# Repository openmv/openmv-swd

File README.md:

# openmv-swd
Serial Wire Debugger Programmer

The Serial Wire Debugger (SWD) Programmer can load firmware on up to five STM32F427/STM32F765/STM32H743 microcontrollers at the same time. The SWD Programmer is powered by the Propeller Chip. All eight cores of the Propeller Chip are used by the SWD Programmer firmware. Each SWD programming thread is run in a separate core. A master core controls the five SWD programming cores. Finally, one core provides SD card services while another core handles button debouncing and LED PWM.

If you're interested in practical code demonstrating how to load the firmware on an ST32F427/STM32F765/STM32H743 microcontroller, or generally, any ST Cortex-M4/Cortex-M7 device checkout the [SWD Code](http://github.com/openmv/openmv-swd/blob/master/module/V2/src/SWD.spin).

# openmv-swd application

* Install 7-Zip and add it to PATH.
* Install Python 2.7 and add it to PATH.
* Install Qt (to the default location).
* Install The Qt Installer Framework (to the default location).

In `/`, build the application (using the standard bare terminal):

     make.py

You'll find the installer in `module/build`.

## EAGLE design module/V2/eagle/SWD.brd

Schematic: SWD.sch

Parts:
3.3V_1,1, 3.3V_1,2, 3.3V_1,3, 3.3V_1,4, 3.3V_2,1, 3.3V_2,2, 3.3V_2,3, 3.3V_2,4, 3.3V_3,1, 3.3V_3,2, 3.3V_3,3, 3.3V_3,4, 3.3V_4,1, 3.3V_4,2, 3.3V_4,3, 3.3V_4,4, 3.3V_5,1, 3.3V_5,2, 3.3V_5,3, 3.3V_5,4: POGO_PIN_0908-4-15-20-75-14-11-0; 0908-4-15-20-75-14-11-0
C1, C2, C3, C4, C5, C6, C7, C10, C12, C13, C15, C16, C17, C18, C19, C20, C21, C22, C23, C24, C25, C27, C28, C29, C30, C31, C32, C33, C34, C35, C61, C62: 0.1uF; C0603
C8, C9: 47pF; C0603
C11, C14: 1uF; C0603
C26: 0.1uF\; C0603
C36, C37, C38, C39: 100uF; CP6.3MM
D1, D2, D3: MF-LED-0805-RED; LED0805
D4: SMBJ5.0CA; SMBJ
FRAME1: MF_FRAMEDEFAULT; MF_FRAME_DEFAULT
GND_1,1, GND_1,2, GND_1,3, GND_1,4, GND_2,1, GND_2,2, GND_2,3, GND_2,4, GND_3,1, GND_3,2, GND_3,3, GND_3,4, GND_4,1, GND_4,2, GND_4,3, GND_4,4, GND_5,1, GND_5,2, GND_5,3, GND_5,4: POGO_PIN_0908-4-15-20-75-14-11-0; 0908-4-15-20-75-14-11-0
J1: USB_TYPE-C_105450-0101; 105450-0101
J2: KLDX-0202-A; DC_PWR_JACK
L1, L2: MI0603K300R-10; L0603
R1, R2, R3, R4, R5, R6, R7, R8, R9, R14, R30, R31, R32, R33: 10K; R0603
R10: 5.1K; R0603
R11, R12: 27; R0603
R13: 4.7K; R0603
R15, R16, R17, R18, R19, R20, R21, R22, R23, R24, R25, R26, R27, R28, R29: 100; R0603
R34, R35, R36: 360; R0603
SD1: MF-MICROSD
SW1, SW2: MF-SW-TACT-6MM; TACT6MM
SWD_CLK_1,1, SWD_CLK_1,2, SWD_CLK_1,3, SWD_CLK_1,4, SWD_CLK_2,1, SWD_CLK_2,2, SWD_CLK_2,3, SWD_CLK_2,4, SWD_CLK_3,1, SWD_CLK_3,2, SWD_CLK_3,3, SWD_CLK_3,4, SWD_CLK_4,1, SWD_CLK_4,2, SWD_CLK_4,3, SWD_CLK_4,4, SWD_CLK_5,1, SWD_CLK_5,2, SWD_CLK_5,3, SWD_CLK_5,4: POGO_PIN_0908-4-15-20-75-14-11-0; 0908-4-15-20-75-14-11-0
SWD_DAT_1,1, SWD_DAT_1,2, SWD_DAT_1,3, SWD_DAT_1,4, SWD_DAT_2,1, SWD_DAT_2,2, SWD_DAT_2,3, SWD_DAT_2,4, SWD_DAT_3,1, SWD_DAT_3,2, SWD_DAT_3,3, SWD_DAT_3,4, SWD_DAT_4,1, SWD_DAT_4,2, SWD_DAT_4,3, SWD_DAT_4,4, SWD_DAT_5,1, SWD_DAT_5,2, SWD_DAT_5,3, SWD_DAT_5,4: POGO_PIN_0908-4-15-20-75-14-11-0; 0908-4-15-20-75-14-11-0
SWD_RST_1,1, SWD_RST_1,2, SWD_RST_1,3, SWD_RST_1,4, SWD_RST_2,1, SWD_RST_2,2, SWD_RST_2,3, SWD_RST_2,4, SWD_RST_3,1, SWD_RST_3,2, SWD_RST_3,3, SWD_RST_3,4, SWD_RST_4,1, SWD_RST_4,2, SWD_RST_4,3, SWD_RST_4,4, SWD_RST_5,1, SWD_RST_5,2, SWD_RST_5,3, SWD_RST_5,4: POGO_PIN_0908-4-15-20-75-14-11-0; 0908-4-15-20-75-14-11-0
U1: P8X32A-Q44; LQFP44
U2: CAT24C512WI-GT3; SOIC-8_W
U3: FT230XQ-R; FT230X_QFN-16
U4, U5, U6, U7, U8, U9, U10, U11, U12, U13, U14, U15, U16, U17, U18, U19, U20, U21, U22, U23: SN74LV4066APWR; SN74LV4066A_TSSOP-14
U24, U25, U26, U27: SSM6J507NU,LF; SSM6J507NU
U$59: MF_LOGOLOGO_TEXT; MF_LOGO_TEXT
UNIT1, UNIT2, UNIT3, UNIT4, UNIT5, UNIT6, UNIT7, UNIT8, UNIT9, UNIT10, UNIT11, UNIT12, UNIT13, UNIT14, UNIT15, UNIT16, UNIT17, UNIT18, UNIT19, UNIT20: OPENMV3
X1: ABMM-6.000MHZ-B2-T; 7MMX5MM

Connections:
3.3V: C1.P$1, C2.P$1, C3.P$1, C4.P$1, C5.P$1, C6.P$1, C7.P$1, C13.P$1, C14.P$1, C16.P$2, C17.P$2, C18.P$2, C19.P$2, C20.P$2, C21.P$2, C22.P$2, C23.P$2, C24.P$2, C25.P$2, C26.P$2, C27.P$2, C28.P$2, C29.P$2, C30.P$2, C31.P$2, C32.P$2, C33.P$2, C34.P$2, C35.P$2, C36.P$1, C37.P$1, C38.P$1, C39.P$1, C61.P$1, C62.P$1, D1.ANODE, D2.ANODE, D3.ANODE, D4.CATH (CATHODE), J2.PIN, R1.P$1, R2.P$1, R3.P$1, R4.P$1, R5.P$1, R6.P$1, R7.P$1, R8.P$1, R9.P$1, R30.P$1, R31.P$1, R32.P$1, R33.P$1, SD1.PIN4 (3.3V), U1.8 (VDD), U1.18 (VDD), U1.30 (VDD), U1.40 (VDD), U2.8 (VCC), U3.1 (VCCIO), U3.9 (RESET#), U3.10 (VCC), U4.P$14 (VCC), U5.P$14 (VCC), U6.P$14 (VCC), U7.P$14 (VCC), U8.P$14 (VCC), U9.P$14 (VCC), U10.P$14 (VCC), U11.P$14 (VCC), U12.P$14 (VCC), U13.P$14 (VCC), U14.P$14 (VCC), U15.P$14 (VCC), U16.P$14 (VCC), U17.P$14 (VCC), U18.P$14 (VCC), U19.P$14 (VCC), U20.P$14 (VCC), U21.P$14 (VCC), U22.P$14 (VCC), U23.P$14 (VCC), U24.P$1 (DRAIN), U24.P$2 (DRAIN), U24.P$5 (DRAIN), U24.P$6 (DRAIN), U24.P$8 (DRAIN), U25.P$1 (DRAIN), U25.P$2 (DRAIN), U25.P$5 (DRAIN), U25.P$6 (DRAIN), U25.P$8 (DRAIN), U26.P$1 (DRAIN), U26.P$2 (DRAIN), U26.P$5 (DRAIN), U26.P$6 (DRAIN), U26.P$8 (DRAIN), U27.P$1 (DRAIN), U27.P$2 (DRAIN), U27.P$5 (DRAIN), U27.P$6 (DRAIN), U27.P$8 (DRAIN)
3.3V_R1: 3.3V_1,1.P$1, 3.3V_2,1.P$1, 3.3V_3,1.P$1, 3.3V_4,1.P$1, 3.3V_5,1.P$1, U24.P$4 (SOURCE), U24.P$7 (SOURCE)
3.3V_R2: 3.3V_1,2.P$1, 3.3V_2,2.P$1, 3.3V_3,2.P$1, 3.3V_4,2.P$1, 3.3V_5,2.P$1, U25.P$4 (SOURCE), U25.P$7 (SOURCE)
3.3V_R3: 3.3V_1,3.P$1, 3.3V_2,3.P$1, 3.3V_3,3.P$1, 3.3V_4,3.P$1, 3.3V_5,3.P$1, U26.P$4 (SOURCE), U26.P$7 (SOURCE)
3.3V_R4: 3.3V_1,4.P$1, 3.3V_2,4.P$1, 3.3V_3,4.P$1, 3.3V_4,4.P$1, 3.3V_5,4.P$1, U27.P$4 (SOURCE), U27.P$7 (SOURCE)
3V3OUT: C12.P$1, U3.8 (3V3OUT)
!RTS: C15.P$1, U3.16 (RTS#)
CC1: J1.A5 (CC1), R10.P$1
CTRL_ROW_1: U1.44 (P3), U4.P$5 (CNTRL), U4.P$6 (CNTRL), U4.P$13 (CNTRL), U8.P$5 (CNTRL), U8.P$6 (CNTRL), U8.P$13 (CNTRL), U12.P$5 (CNTRL), U12.P$6 (CNTRL), U12.P$13 (CNTRL), U16.P$5 (CNTRL), U16.P$6 (CNTRL), U16.P$13 (CNTRL), U20.P$5 (CNTRL), U20.P$6 (CNTRL), U20.P$13 (CNTRL)
CTRL_ROW_2: U1.43 (P2), U5.P$5 (CNTRL), U5.P$6 (CNTRL), U5.P$13 (CNTRL), U9.P$5 (CNTRL), U9.P$6 (CNTRL), U9.P$13 (CNTRL), U13.P$5 (CNTRL), U13.P$6 (CNTRL), U13.P$13 (CNTRL), U17.P$5 (CNTRL), U17.P$6 (CNTRL), U17.P$13 (CNTRL), U21.P$5 (CNTRL), U21.P$6 (CNTRL), U21.P$13 (CNTRL)
CTRL_ROW_3: U1.42 (P1), U6.P$5 (CNTRL), U6.P$6 (CNTRL), U6.P$13 (CNTRL), U10.P$5 (CNTRL), U10.P$6 (CNTRL), U10.P$13 (CNTRL), U14.P$5 (CNTRL), U14.P$6 (CNTRL), U14.P$13 (CNTRL), U18.P$5 (CNTRL), U18.P$6 (CNTRL), U18.P$13 (CNTRL), U22.P$5 (CNTRL), U22.P$6 (CNTRL), U22.P$13 (CNTRL)
CTRL_ROW_4: U1.41 (P0), U7.P$5 (CNTRL), U7.P$6 (CNTRL), U7.P$13 (CNTRL), U11.P$5 (CNTRL), U11.P$6 (CNTRL), U11.P$13 (CNTRL), U15.P$5 (CNTRL), U15.P$6 (CNTRL), U15.P$13 (CNTRL), U19.P$5 (CNTRL), U19.P$6 (CNTRL), U19.P$13 (CNTRL), U23.P$5 (CNTRL), U23.P$6 (CNTRL), U23.P$13 (CNTRL)
D+: C8.P$1, J1.A6 (D+), J1.B6 (D+), R11.P$1
D-: C9.P$1, J1.A7 (D-), J1.B7 (D-), R12.P$1
GND: C1.P$2, C2.P$2, C3.P$2, C4.P$2, C5.P$2, C6.P$2, C7.P$2, C8.P$2, C9.P$2, C10.P$2, C11.P$2, C12.P$2, C13.P$2, C14.P$2, C16.P$1, C17.P$1, C18.P$1, C19.P$1, C20.P$1, C21.P$1, C22.P$1, C23.P$1, C24.P$1, C25.P$1, C26.P$1, C27.P$1, C28.P$1, C29.P$1, C30.P$1, C31.P$1, C32.P$1, C33.P$1, C34.P$1, C35.P$1, C36.P$2, C37.P$2, C38.P$2, C39.P$2, C61.P$2, C62.P$2, D4.ANODE, GND_1,1.P$1, GND_1,2.P$1, GND_1,3.P$1, GND_1,4.P$1, GND_2,1.P$1, GND_2,2.P$1, GND_2,3.P$1, GND_2,4.P$1, GND_3,1.P$1, GND_3,2.P$1, GND_3,3.P$1, GND_3,4.P$1, GND_4,1.P$1, GND_4,2.P$1, GND_4,3.P$1, GND_4,4.P$1, GND_5,1.P$1, GND_5,2.P$1, GND_5,3.P$1, GND_5,4.P$1, J1.A1 (GND), J1.A12 (GND), J1.B1 (GND), J1.B12 (GND), J2.SLEEVE1 (SLEEVE), J2.SLEEVE2 (SLEEVE_SHUNT), L2.P$2, R10.P$2, R14.P$1, R35.P$2, SD1.G0 (GND), SD1.G1 (GND), SD1.PIN6 (GND), SW1.P$3, U1.5 (VSS), U1.6 (BOE'), U1.17 (VSS), U1.27 (VSS), U1.39 (VSS), U2.1 (A0), U2.2 (A1), U2.3 (A2), U2.4 (GND), U2.7 (WP), U3.3 (GND), U3.13 (GND), U3.PAD (GND), U4.P$7 (GND), U5.P$7 (GND), U6.P$7 (GND), U7.P$7 (GND), U8.P$7 (GND), U9.P$7 (GND), U10.P$7 (GND), U11.P$7 (GND), U12.P$7 (GND), U13.P$7 (GND), U14.P$7 (GND), U15.P$7 (GND), U16.P$7 (GND), U17.P$7 (GND), U18.P$7 (GND), U19.P$7 (GND), U20.P$7 (GND), U21.P$7 (GND), U22.P$7 (GND), U23.P$7 (GND), X1.P$2 (GND), X1.P$4 (GND)
I2C_SCL: R9.P$2, U1.35 (P28), U2.6 (SCL)
I2C_SDA: R8.P$2, U1.36 (P29), U2.5 (SDA)
IRQ: R2.P$2, SD1.PIN8 (IRQ)
LED_HB: R36.P$2, U1.26 (P23)
unnamed: R16.P$1, U4.P$4 (A), U5.P$4 (A), U6.P$4 (A), U7.P$4 (A)
unnamed: R18.P$1, U8.P$1 (A), U9.P$1 (A), U10.P$1 (A), U11.P$1 (A)
unnamed: R15.P$1, U4.P$1 (A), U5.P$1 (A), U6.P$1 (A), U7.P$1 (A)
unnamed: R20.P$1, U8.P$8 (A), U9.P$8 (A), U10.P$8 (A), U11.P$8 (A)
unnamed: R19.P$1, U8.P$4 (A), U9.P$4 (A), U10.P$4 (A), U11.P$4 (A)
unnamed: R21.P$1, U12.P$1 (A), U13.P$1 (A), U14.P$1 (A), U15.P$1 (A)
unnamed: R23.P$1, U12.P$8 (A), U13.P$8 (A), U14.P$8 (A), U15.P$8 (A)
unnamed: R17.P$1, U4.P$8 (A), U5.P$8 (A), U6.P$8 (A), U7.P$8 (A)
unnamed: R22.P$1, U12.P$4 (A), U13.P$4 (A), U14.P$4 (A), U15.P$4 (A)
unnamed: R24.P$1, U16.P$1 (A), U17.P$1 (A), U18.P$1 (A), U19.P$1 (A)
unnamed: R26.P$1, U16.P$8 (A), U17.P$8 (A), U18.P$8 (A), U19.P$8 (A)
unnamed: R25.P$1, U16.P$4 (A), U17.P$4 (A), U18.P$4 (A), U19.P$4 (A)
unnamed: R27.P$1, U20.P$1 (A), U21.P$1 (A), U22.P$1 (A), U23.P$1 (A)
unnamed: R29.P$1, U20.P$8 (A), U21.P$8 (A), U22.P$8 (A), U23.P$8 (A)
unnamed: R28.P$1, U20.P$4 (A), U21.P$4 (A), U22.P$4 (A), U23.P$4 (A)
unnamed: D3.CATHODE, R36.P$1
unnamed: D2.CATHODE, R35.P$1
unnamed: C15.P$2, SW2.P$1
unnamed: D1.CATHODE, R34.P$1
PWR_1: R30.P$2, U1.22 (P19), U24.P$3 (GATE)
PWR_2: R31.P$2, U1.23 (P20), U25.P$3 (GATE)
PWR_3: R32.P$2, U1.24 (P21), U26.P$3 (GATE)
PWR_4: R33.P$2, U1.25 (P22), U27.P$3 (GATE)
RES: R1.P$2, SW1.P$2, SW2.P$4, U1.7 (RES')
RW: R7.P$2, SD1.PIN1 (RW)
RX: U1.37 (P30), U3.2 (RXD)
SD_CLK: R4.P$2, SD1.PIN5 (SCLK), U1.32 (P25)
SD_CS: R6.P$2, SD1.PIN2 (CS), U1.34 (P27)
SD_DI: R5.P$2, SD1.PIN3 (DI), U1.33 (P26)
SD_DO: R3.P$2, SD1.PIN7 (D0), U1.31 (P24)
SHLD: J1.S_T1 (SHLD), J1.S_T2 (SHLD), J1.S_T3 (SHLD), J1.S_T4 (SHLD), L2.P$1
SWD_CLK_1: R15.P$2, U1.1 (P4)
SWD_CLK_1,1: SWD_CLK_1,1.P$1, U4.P$2 (B)
SWD_CLK_1,2: SWD_CLK_1,2.P$1, U5.P$2 (B)
SWD_CLK_1,3: SWD_CLK_1,3.P$1, U6.P$2 (B)
SWD_CLK_1,4: SWD_CLK_1,4.P$1, U7.P$2 (B)
SWD_CLK_2: R18.P$2, U1.4 (P7)
SWD_CLK_2,1: SWD_CLK_2,1.P$1, U8.P$2 (B)
SWD_CLK_2,2: SWD_CLK_2,2.P$1, U9.P$2 (B)
SWD_CLK_2,3: SWD_CLK_2,3.P$1, U10.P$2 (B)
SWD_CLK_2,4: SWD_CLK_2,4.P$1, U11.P$2 (B)
SWD_CLK_3: R21.P$2, U1.11 (P10)
SWD_CLK_3,1: SWD_CLK_3,1.P$1, U12.P$2 (B)
SWD_CLK_3,2: SWD_CLK_3,2.P$1, U13.P$2 (B)
SWD_CLK_3,3: SWD_CLK_3,3.P$1, U14.P$2 (B)
SWD_CLK_3,4: SWD_CLK_3,4.P$1, U15.P$2 (B)
SWD_CLK_4: R24.P$2, U1.14 (P13)
SWD_CLK_4,1: SWD_CLK_4,1.P$1, U16.P$2 (B)
SWD_CLK_4,2: SWD_CLK_4,2.P$1, U17.P$2 (B)
SWD_CLK_4,3: SWD_CLK_4,3.P$1, U18.P$2 (B)
SWD_CLK_4,4: SWD_CLK_4,4.P$1, U19.P$2 (B)
SWD_CLK_5: R27.P$2, U1.19 (P16)
SWD_CLK_5,1: SWD_CLK_5,1.P$1, U20.P$2 (B)
SWD_CLK_5,2: SWD_CLK_5,2.P$1, U21.P$2 (B)
SWD_CLK_5,3: SWD_CLK_5,3.P$1, U22.P$2 (B)
SWD_CLK_5,4: SWD_CLK_5,4.P$1, U23.P$2 (B)
SWD_DAT_1: R16.P$2, U1.2 (P5)
SWD_DAT_1,1: SWD_DAT_1,1.P$1, U4.P$3 (B)
SWD_DAT_1,2: SWD_DAT_1,2.P$1, U5.P$3 (B)
SWD_DAT_1,3: SWD_DAT_1,3.P$1, U6.P$3 (B)
SWD_DAT_1,4: SWD_DAT_1,4.P$1, U7.P$3 (B)
SWD_DAT_2: R19.P$2, U1.9 (P8)
SWD_DAT_2,1: SWD_DAT_2,1.P$1, U8.P$3 (B)
SWD_DAT_2,2: SWD_DAT_2,2.P$1, U9.P$3 (B)
SWD_DAT_2,3: SWD_DAT_2,3.P$1, U10.P$3 (B)
SWD_DAT_2,4: SWD_DAT_2,4.P$1, U11.P$3 (B)
SWD_DAT_3: R22.P$2, U1.12 (P11)
SWD_DAT_3,1: SWD_DAT_3,1.P$1, U12.P$3 (B)
SWD_DAT_3,2: SWD_DAT_3,2.P$1, U13.P$3 (B)
SWD_DAT_3,3: SWD_DAT_3,3.P$1, U14.P$3 (B)
SWD_DAT_3,4: SWD_DAT_3,4.P$1, U15.P$3 (B)
SWD_DAT_4: R25.P$2, U1.15 (P14)
SWD_DAT_4,1: SWD_DAT_4,1.P$1, U16.P$3 (B)
SWD_DAT_4,2: SWD_DAT_4,2.P$1, U17.P$3 (B)
SWD_DAT_4,3: SWD_DAT_4,3.P$1, U18.P$3 (B)
SWD_DAT_4,4: SWD_DAT_4,4.P$1, U19.P$3 (B)
SWD_DAT_5: R28.P$2, U1.20 (P17)
SWD_DAT_5,1: SWD_DAT_5,1.P$1, U20.P$3 (B)
SWD_DAT_5,2: SWD_DAT_5,2.P$1, U21.P$3 (B)
SWD_DAT_5,3: SWD_DAT_5,3.P$1, U22.P$3 (B)
SWD_DAT_5,4: SWD_DAT_5,4.P$1, U23.P$3 (B)
SWD_RST_1: R17.P$2, U1.3 (P6)
SWD_RST_1,1: SWD_RST_1,1.P$1, U4.P$9 (B)
SWD_RST_1,2: SWD_RST_1,2.P$1, U5.P$9 (B)
SWD_RST_1,3: SWD_RST_1,3.P$1, U6.P$9 (B)
SWD_RST_1,4: SWD_RST_1,4.P$1, U7.P$9 (B)
SWD_RST_2: R20.P$2, U1.10 (P9)
SWD_RST_2,1: SWD_RST_2,1.P$1, U8.P$9 (B)
SWD_RST_2,2: SWD_RST_2,2.P$1, U9.P$9 (B)
SWD_RST_2,3: SWD_RST_2,3.P$1, U10.P$9 (B)
SWD_RST_2,4: SWD_RST_2,4.P$1, U11.P$9 (B)
SWD_RST_3: R23.P$2, U1.13 (P12)
SWD_RST_3,1: SWD_RST_3,1.P$1, U12.P$9 (B)
SWD_RST_3,2: SWD_RST_3,2.P$1, U13.P$9 (B)
SWD_RST_3,3: SWD_RST_3,3.P$1, U14.P$9 (B)
SWD_RST_3,4: SWD_RST_3,4.P$1, U15.P$9 (B)
SWD_RST_4: R26.P$2, U1.16 (P15)
SWD_RST_4,1: SWD_RST_4,1.P$1, U16.P$9 (B)
SWD_RST_4,2: SWD_RST_4,2.P$1, U17.P$9 (B)
SWD_RST_4,3: SWD_RST_4,3.P$1, U18.P$9 (B)
SWD_RST_4,4: SWD_RST_4,4.P$1, U19.P$9 (B)
SWD_RST_5: R29.P$2, U1.21 (P18)
SWD_RST_5,1: SWD_RST_5,1.P$1, U20.P$9 (B)
SWD_RST_5,2: SWD_RST_5,2.P$1, U21.P$9 (B)
SWD_RST_5,3: SWD_RST_5,3.P$1, U22.P$9 (B)
SWD_RST_5,4: SWD_RST_5,4.P$1, U23.P$9 (B)
TX: U1.38 (P31), U3.15 (TXD)
TXRX_LED: R34.P$2, U3.5 (CBUS2)
USBDM: R12.P$2, U3.7 (USBDM)
USBDP: R11.P$2, U3.6 (USBDP)
VBUS_SENSE: R13.P$1, R14.P$2, U3.12 (CBUS0)
V_USB: J1.A4 (VBUS), J1.A9 (VBUS), J1.B4 (VBUS), J1.B9 (VBUS), L1.P$1
V_USB_SENSE: C10.P$1, C11.P$1, L1.P$2, R13.P$2
X0: U1.29 (X0), X1.P$3 (X1)
X1: U1.28 (X1), X1.P$1 (X0)

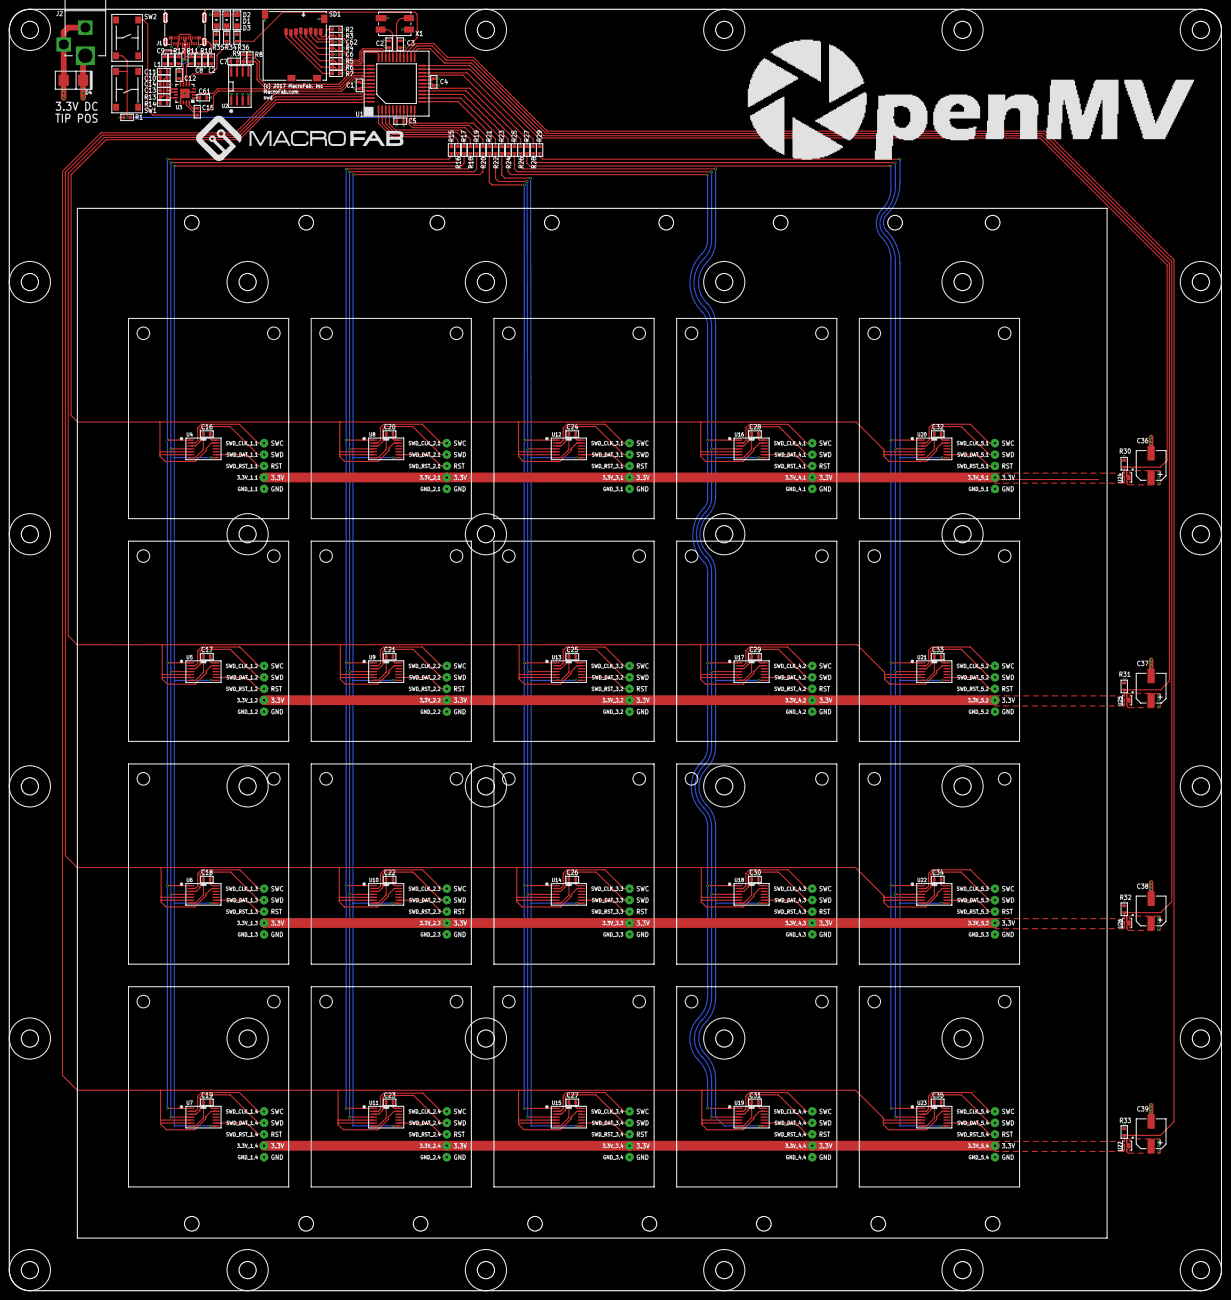
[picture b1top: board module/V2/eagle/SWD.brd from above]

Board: 4 copper layers, 269.1 x 284.5 mm, 273 parts (0 on the bottom side), 134 nets.

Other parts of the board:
U$24, U$25, U$26, U$27, U$28, U$29, U$30, U$31, U$32, U$33, U$34, U$35, U$36, U$37, U$38, U$39, U$40, U$41, U$42, U$43, U$44, U$45, U$46, U$47, U$48, U$49, U$50, U$51, U$52, U$53, U$54, U$55, U$56, U$57, U$58: MOUNT_HOLE_150MIL

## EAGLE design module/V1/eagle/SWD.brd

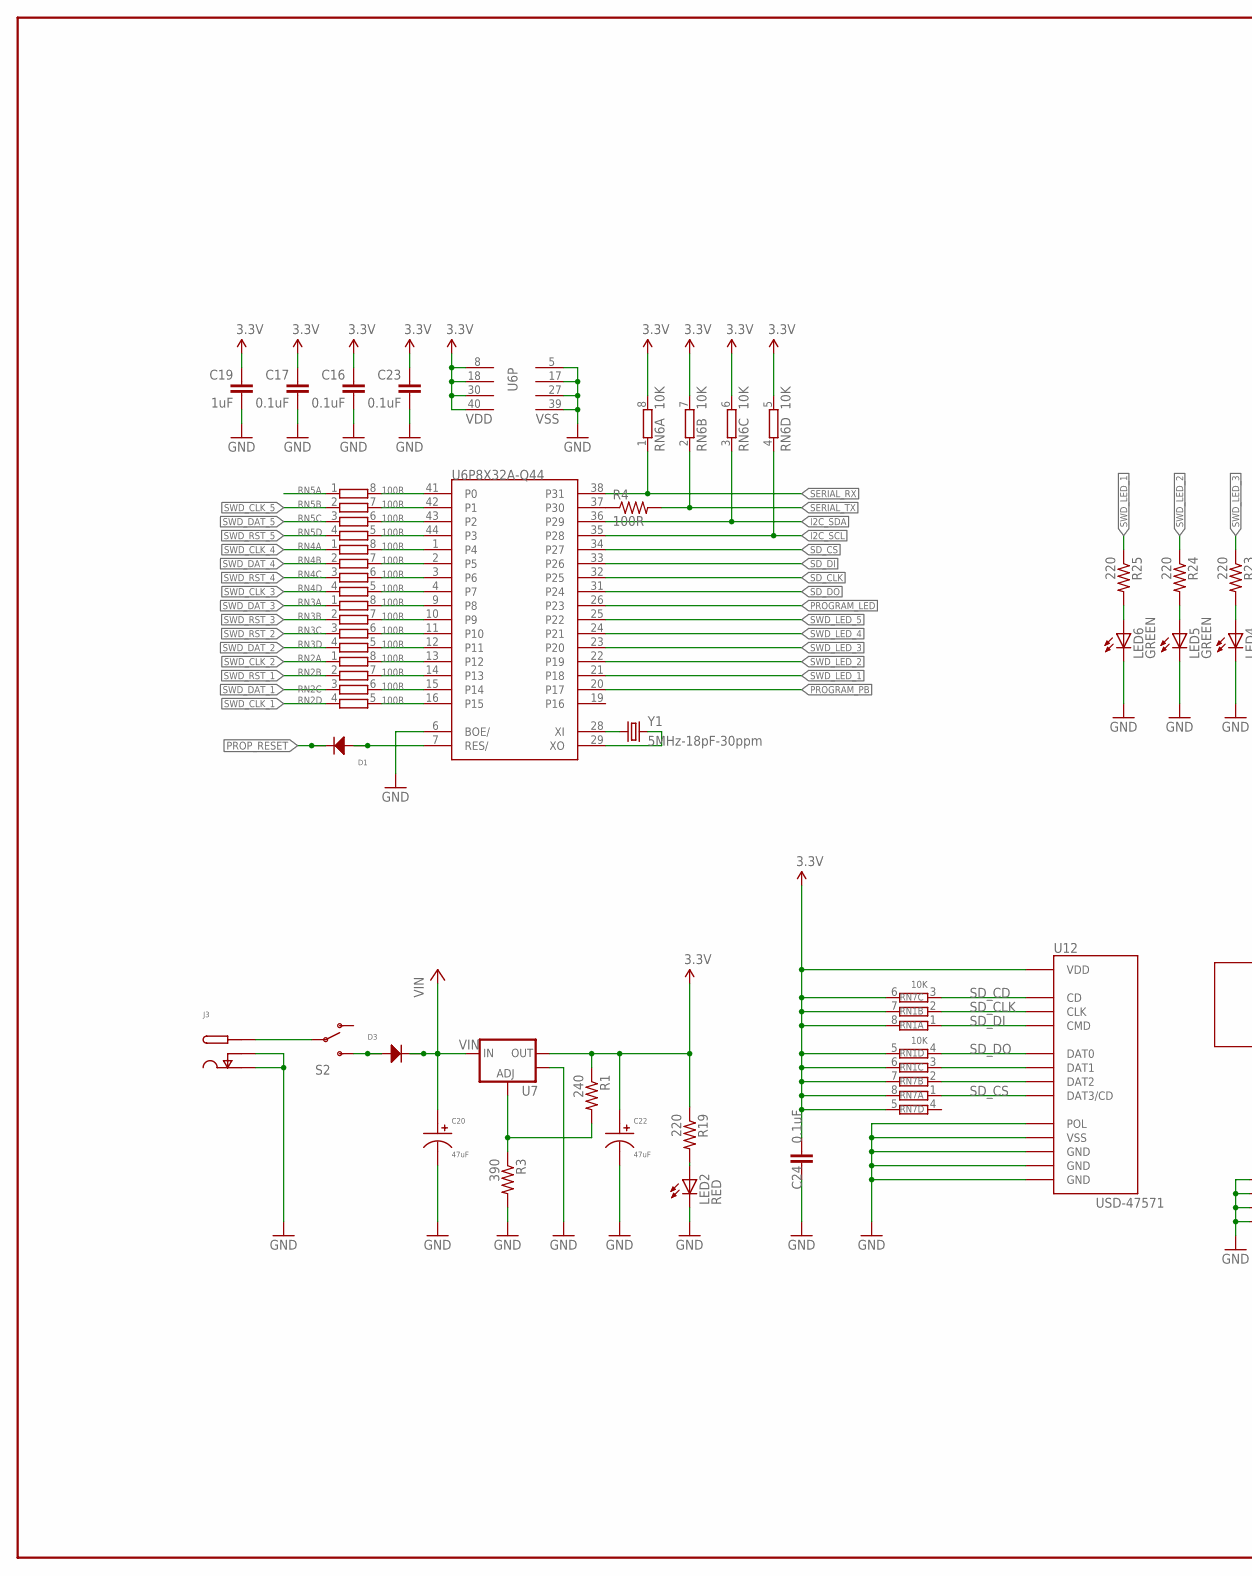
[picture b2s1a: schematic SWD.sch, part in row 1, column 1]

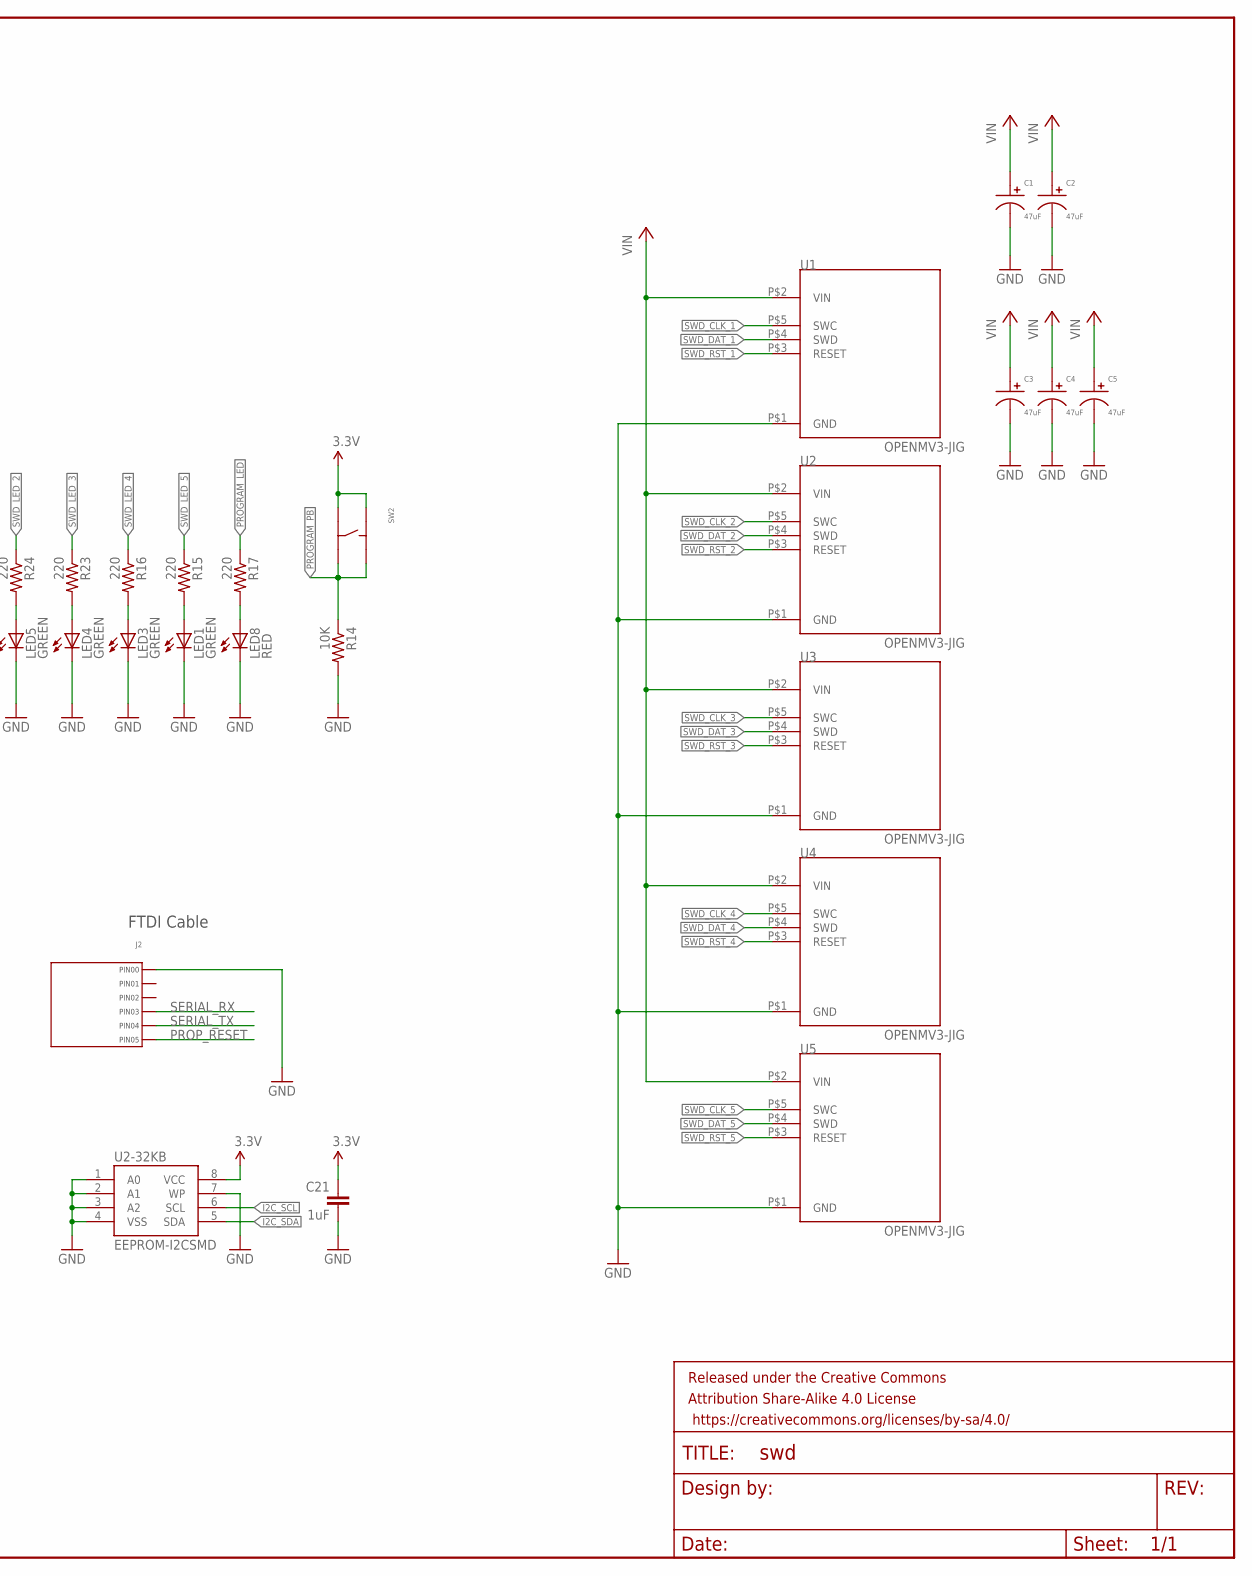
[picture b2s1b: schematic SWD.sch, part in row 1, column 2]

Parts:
C1, C2, C3, C4, C5: 47uF; CP6.3MM; TOLERANCE N/A; MFG# N/A
C16, C17, C23, C24: 0.1uF; 0603-CAP
C19, C21: 1uF; 0603-CAP
C20, C22: 47uF; CP6.3MM
D1: DIODE_SOD-123; SOD-123
D3: DIODE_SMA; SMA
FRAME1: FRAME-LEDGER; CREATIVE_COMMONS
J2: HEADER_01X06_PTH_2.54MM; PTH_2.54MM_01X06
J3: DC_PWR_JACK_2.5MM_RIGHT; DC_PWR_JACK
LED1, LED3, LED4, LED5, LED6: GREEN; LED-0603
LED2, LED8: RED; LED-0603
R1: 240; 0603-RES
R3: 390; 0603-RES
R4: 100R; 0603-RES
R14: 10K; 0603-RES
R15, R16, R17, R19, R23, R24, R25: 220; 0603-RES
RN1, RN6, RN7: 10K; EXBV8V
RN2, RN3, RN4, RN5: 100R; EXBV8V
S2: SWITCH-SPSTPTH; SWITCH-SPDT
SW2: TACT_6MM; TACT6MM
U1, U2, U3, U4, U5: OPENMV3-JIG
U2-32KB: EEPROM-I2CSMD; SO08
U6: P8X32A-Q44
U7: V_REG_LM1117SOT223; SOT223
U12: USD-47571
Y1: 5MHz-18pF-30ppm; HC49UP

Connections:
3.3V: C16.1, C17.1, C19.1, C21.1, C22.P$1, C23.1, C24.1, R1.1, R19.1, RN1.5 (2), RN1.6 (2), RN1.7 (2), RN1.8 (2), RN6.5 (2), RN6.6 (2), RN6.7 (2), RN6.8 (2), RN7.5 (2), RN7.6 (2), RN7.7 (2), RN7.8 (2), SW2.P$1, SW2.P$3, U2-32KB.8 (VCC), U6.8 (VDD), U6.18 (VDD), U6.30 (VDD), U6.40 (VDD), U7.2 (OUT), U12.P$4 (VDD)
GND: C1.P$2, C2.P$2, C3.P$2, C4.P$2, C5.P$2, C16.2, C17.2, C19.2, C20.P$2, C21.2, C22.P$2, C23.2, C24.2, J2.P$1 (PIN0), J3.SLEEVE1 (SLEEVE), J3.SLEEVE2 (SLEEVE_SHUNT), LED1.C, LED2.C, LED3.C, LED4.C, LED5.C, LED6.C, LED8.C, R3.2, R14.2, U1.P$1 (GND), U2.P$1 (GND), U2-32KB.1 (A0), U2-32KB.2 (A1), U2-32KB.3 (A2), U2-32KB.4 (VSS), U2-32KB.7 (WP), U3.P$1 (GND), U4.P$1 (GND), U5.P$1 (GND), U6.5 (VSS), U6.6 (BOE/), U6.17 (VSS), U6.27 (VSS), U6.39 (VSS), U7.4 (OUT), U12.G$1 (GND), U12.G$2 (GND), U12.G$3 (GND), U12.G$4 (POL), U12.P$6 (VSS)
I2C_SCL: RN6.4 (1), U2-32KB.6 (SCL), U6.35 (P28)
I2C_SDA: RN6.3 (1), U2-32KB.5 (SDA), U6.36 (P29)
unnamed: R4.1, U6.37 (P30)
unnamed: D3.ANODE, S2.3 (S)
unnamed: U6.28 (XI), Y1.1
unnamed: U6.29 (XO), Y1.2
unnamed: LED2.A, R19.2
unnamed: D1.ANODE, U6.7 (RES/)
unnamed: J3.PIN, S2.2
unnamed: RN1.3 (1), U12.P$8 (DAT1)
unnamed: RN7.2 (1), U12.P$1 (DAT2)
unnamed: LED6.A, R25.2
unnamed: LED5.A, R24.2
unnamed: LED4.A, R23.2
unnamed: LED3.A, R16.2
unnamed: LED1.A, R15.2
unnamed: LED8.A, R17.2
unnamed: RN2.8 (2), U6.13 (P12)
unnamed: RN2.7 (2), U6.14 (P13)
unnamed: RN2.6 (2), U6.15 (P14)
unnamed: RN2.5 (2), U6.16 (P15)
unnamed: RN3.5 (2), U6.12 (P11)
unnamed: RN3.6 (2), U6.11 (P10)
unnamed: RN3.7 (2), U6.10 (P9)
unnamed: RN3.8 (2), U6.9 (P8)
unnamed: R1.2, R3.1, U7.1 (ADJ)
unnamed: RN5.6 (2), U6.43 (P2)
unnamed: RN5.7 (2), U6.42 (P1)
unnamed: RN5.8 (2), U6.41 (P0)
unnamed: RN5.5 (2), U6.44 (P3)
unnamed: RN4.8 (2), U6.1 (P4)
unnamed: RN4.7 (2), U6.2 (P5)
unnamed: RN4.6 (2), U6.3 (P6)
unnamed: RN4.5 (2), U6.4 (P7)
PROGRAM_LED: R17.1, U6.26 (P23)
PROGRAM_PB: R14.1, SW2.P$2, SW2.P$4, U6.20 (P17)
PROP_RESET: D1.CATHODE, J2.P$6 (PIN5)
SD_CD: RN7.3 (1), U12.G$5 (CD)
SD_CLK: RN1.2 (1), U6.32 (P25), U12.P$5 (CLK)
SD_CS: RN7.1, U6.34 (P27), U12.P$2 (DAT3/CD)
SD_DI: RN1.1, U6.33 (P26), U12.P$3 (CMD)
SD_DO: RN1.4 (1), U6.31 (P24), U12.P$7 (DAT0)
SERIAL_RX: J2.P$4 (PIN3), RN6.1, U6.38 (P31)
SERIAL_TX: J2.P$5 (PIN4), R4.2, RN6.2 (1)
SWD_CLK_1: RN2.4 (1), U1.P$5 (SWC)
SWD_CLK_2: RN2.1, U2.P$5 (SWC)
SWD_CLK_3: RN4.4 (1), U3.P$5 (SWC)
SWD_CLK_4: RN4.1, U4.P$5 (SWC)
SWD_CLK_5: RN5.2 (1), U5.P$5 (SWC)
SWD_DAT_1: RN2.3 (1), U1.P$4 (SWD)
SWD_DAT_2: RN3.4 (1), U2.P$4 (SWD)
SWD_DAT_3: RN3.1, U3.P$4 (SWD)
SWD_DAT_4: RN4.2 (1), U4.P$4 (SWD)
SWD_DAT_5: RN5.3 (1), U5.P$4 (SWD)
SWD_LED_1: R25.1, U6.21 (P18)
SWD_LED_2: R24.1, U6.22 (P19)
SWD_LED_3: R23.1, U6.23 (P20)
SWD_LED_4: R16.1, U6.24 (P21)
SWD_LED_5: R15.1, U6.25 (P22)
SWD_RST_1: RN2.2 (1), U1.P$3 (RESET)
SWD_RST_2: RN3.3 (1), U2.P$3 (RESET)
SWD_RST_3: RN3.2 (1), U3.P$3 (RESET)
SWD_RST_4: RN4.3 (1), U4.P$3 (RESET)
SWD_RST_5: RN5.4 (1), U5.P$3 (RESET)
VIN: C1.P$1, C2.P$1, C3.P$1, C4.P$1, C5.P$1, C20.P$1, D3.CATHODE, U1.P$2 (VIN), U2.P$2 (VIN), U3.P$2 (VIN), U4.P$2 (VIN), U5.P$2 (VIN), U7.3 (IN)

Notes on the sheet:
FTDI Cable

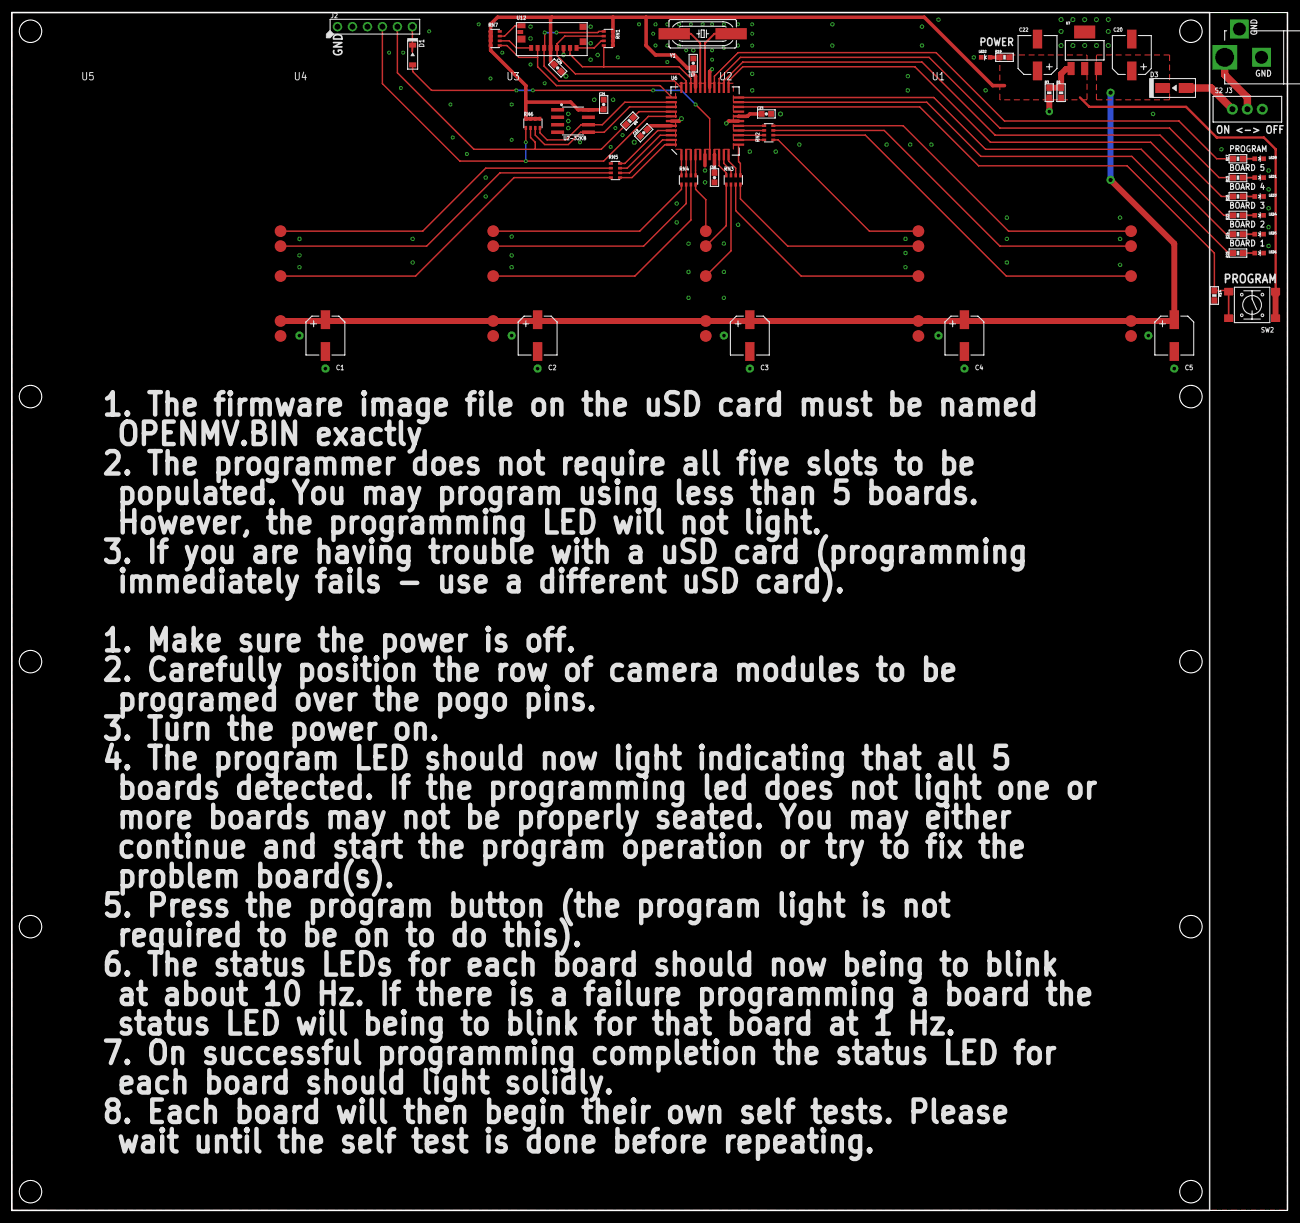
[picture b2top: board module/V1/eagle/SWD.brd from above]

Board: 2 copper layers, 216.4 x 203.2 mm, 55 parts (0 on the bottom side), 67 nets.

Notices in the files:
parts and their libraries:
SparkFun-Aesthetics: Licensing: Creative Commons ShareAlike 4.0 International - https://creativecommons.org/licenses/by-sa/4.0
SparkFun-Aesthetics: Released under the Creative Commons Attribution Share-Alike 4.0 License
SparkFun-Aesthetics: https://creativecommons.org/licenses/by-sa/4.0
